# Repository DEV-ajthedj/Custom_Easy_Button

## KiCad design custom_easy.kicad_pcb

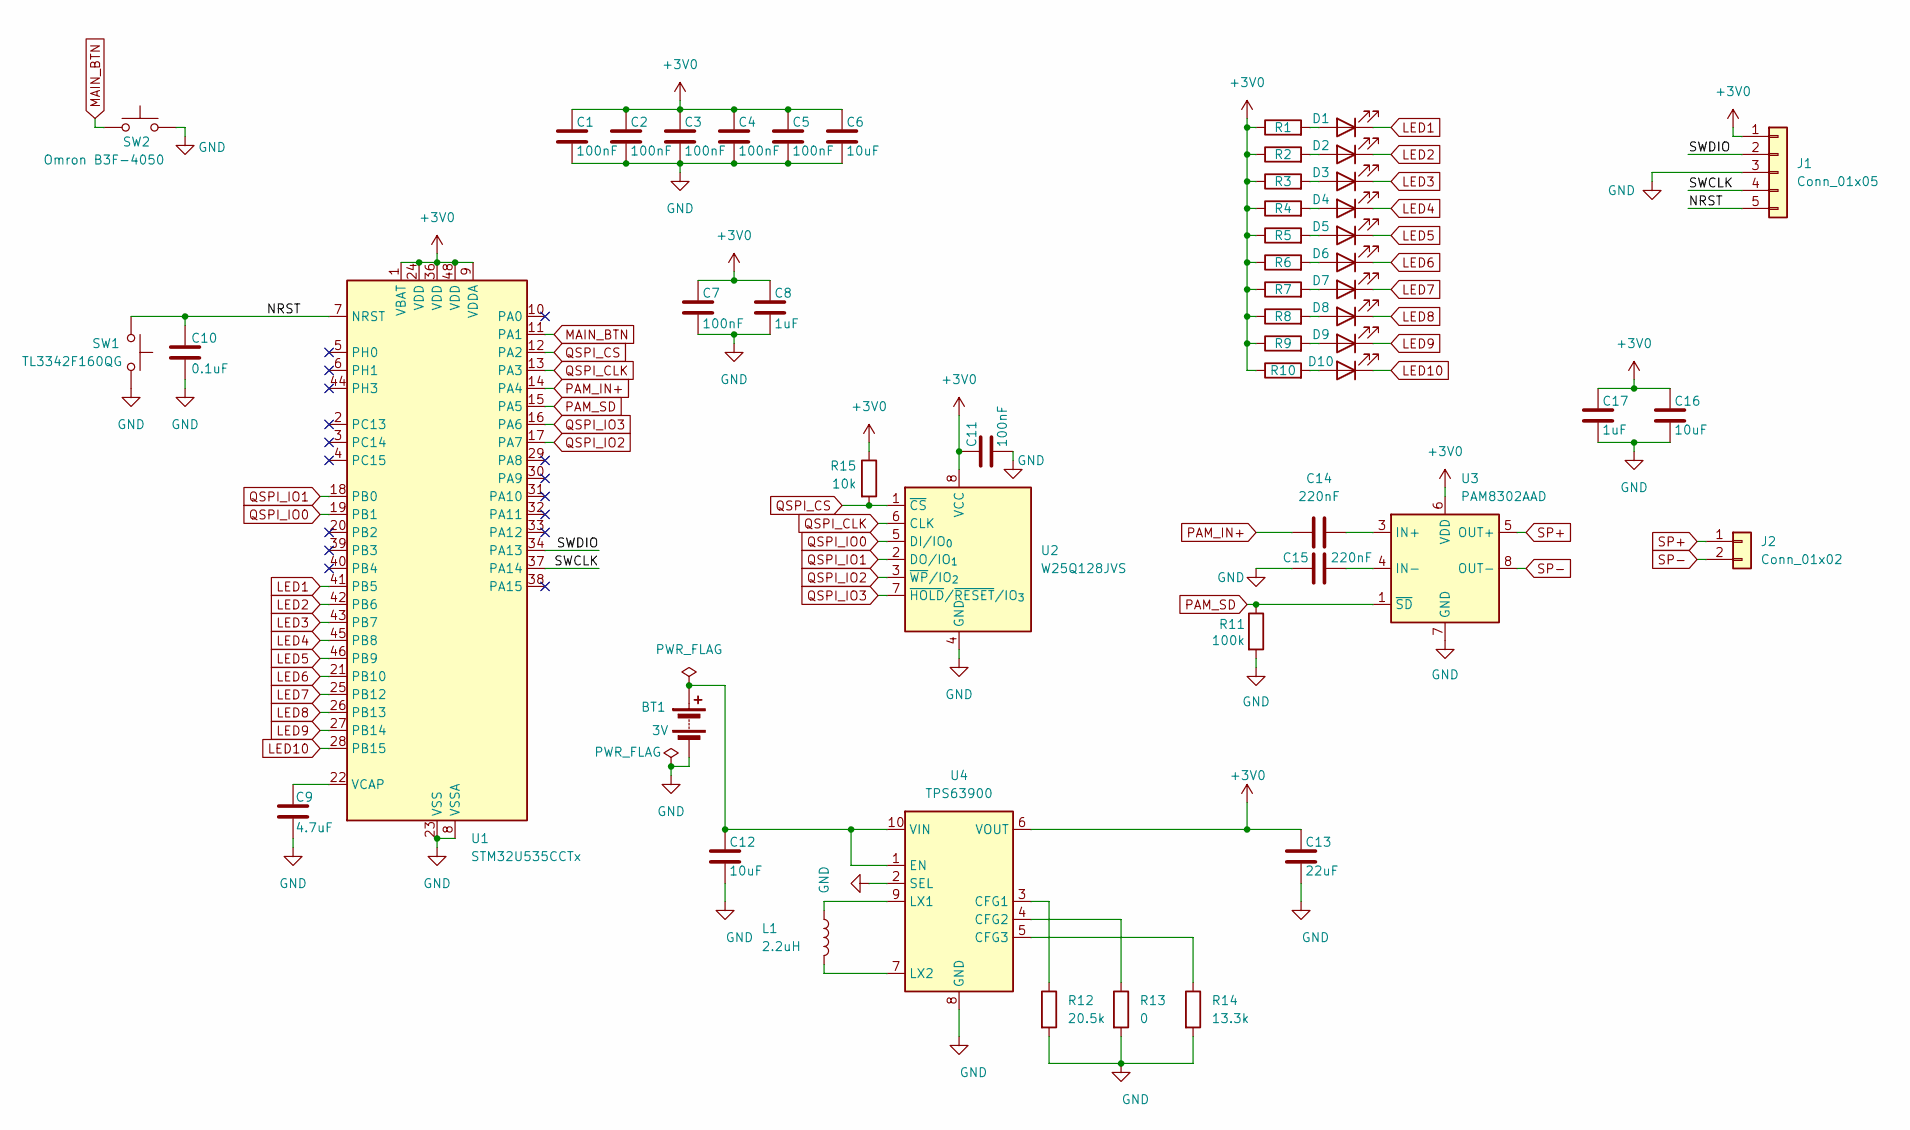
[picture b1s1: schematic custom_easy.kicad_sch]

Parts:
BT1: 3V; SolderWire-0.5sqmm_1x02_P4.6mm_D0.9mm_OD2.1mm
C1, C2, C3, C4, C5, C7, C11: 100nF; C_0603_1608Metric
C6, C16: 10uF; C_0805_2012Metric
C8, C17: 1uF; C_0603_1608Metric
C9: 4.7uF; C_0805_2012Metric
C10: 0.1uF; C_0603_1608Metric
C12: 10uF; C_0603_1608Metric; Voltage 10 V; MPN GRM188R61A106ME69D
C13: 22uF; C_0603_1608Metric; Voltage 6.3 V; MPN GRM187R60J226ME15D
C14, C15: 220nF; C_0603_1608Metric
D1, D2, D3, D4, D5, D6, D7, D8, D9, D10: APTD1608LSECK/J3-PF; LED_0603_1608Metric
J1: Conn_01x05; PinHeader_1x05_P2.54mm_Vertical
J2: Conn_01x02; SolderWire-0.5sqmm_1x02_P4.6mm_D0.9mm_OD2.1mm
L1: 2.2uH; L_Coilcraft_XxL4020; MPN XFL4020-222MEC
R1, R2, R3, R4, R5, R6, R7, R8, R9, R10: 620; R_0603_1608Metric
R11: 100k; R_0603_1608Metric
R12: 20.5k; R_0603_1608Metric; Tolerance 1%
R13: 0; R_0603_1608Metric
R14: 13.3k; R_0603_1608Metric; Tolerance 1%
R15: 10k; R_0603_1608Metric
SW1: TL3342F160QG; SW_SPST_TL3342
SW2: Omron B3F-4050; SW_SPST_Omron_B3F-40xx
U1: STM32U535CCTx; LQFP-48_7x7mm_P0.5mm
U2: W25Q128JVS; SOIC-8_5.3x5.3mm_P1.27mm
U3: PAM8302AAD; SOIC-8_3.9x4.9mm_P1.27mm
U4: TPS63900; WSON-10-1EP_2.5x2.5mm_P0.5mm_EP1.2x2mm_ThermalVias

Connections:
+3V0: C1.1, C2.1, C3.1, C4.1, C5.1, C6.1, C7.1, C8.1, C11.1, C13.1, C16.1, C17.1, J1.1, R1.1, R2.1, R3.1, R4.1, R5.1, R6.1, R7.1, R8.1, R9.1, R10.1, R15.1, U1.1 (VBAT), U1.9 (VDDA), U1.24 (VDD), U1.36 (VDD), U1.48 (VDD), U2.8 (VCC), U3.6 (VDD), U4.6 (VOUT)
/NRST: C10.1, J1.5, SW1.1, U1.7 (NRST)
/SWCLK: J1.4, U1.37 (PA14)
/SWDIO: J1.2, U1.34 (PA13)
GND: BT1.2 (-), C1.2, C2.2, C3.2, C4.2, C5.2, C6.2, C7.2, C8.2, C9.2, C10.2, C11.2, C12.2, C13.2, C15.1, C16.2, C17.2, J1.3, R11.2, R12.2, R13.2, R14.2, SW1.2, SW2.2, U1.8 (VSSA), U1.23 (VSS), U1.35 (VSS), U1.47 (VSS), U2.4 (GND), U3.7 (GND), U4.2 (SEL), U4.8 (GND), U4.11 (GND)
LED1: D1.1 (K), U1.41 (PB5)
LED2: D2.1 (K), U1.42 (PB6)
LED3: D3.1 (K), U1.43 (PB7)
LED4: D4.1 (K), U1.45 (PB8)
LED5: D5.1 (K), U1.46 (PB9)
LED6: D6.1 (K), U1.21 (PB10)
LED7: D7.1 (K), U1.25 (PB12)
LED8: D8.1 (K), U1.26 (PB13)
LED9: D9.1 (K), U1.27 (PB14)
LED10: D10.1 (K), U1.28 (PB15)
MAIN_BTN: SW2.1, U1.11 (PA1)
unnamed: BT1.1 (+), C12.1, U4.1 (EN), U4.10 (VIN)
unnamed: D1.2 (A), R1.2
unnamed: D2.2 (A), R2.2
unnamed: D3.2 (A), R3.2
unnamed: D4.2 (A), R4.2
unnamed: D5.2 (A), R5.2
unnamed: D6.2 (A), R6.2
unnamed: D7.2 (A), R7.2
unnamed: D8.2 (A), R8.2
unnamed: D9.2 (A), R9.2
unnamed: D10.2 (A), R10.2
unnamed: C9.1, U1.22 (VCAP)
unnamed: C14.2, U3.3 (IN+)
unnamed: C15.2, U3.4 (IN-)
unnamed: R12.1, U4.3 (CFG1)
unnamed: R13.1, U4.4 (CFG2)
unnamed: R14.1, U4.5 (CFG3)
unnamed: L1.1, U4.9 (LX1)
unnamed: L1.2, U4.7 (LX2)
PAM_IN+: C14.1, U1.14 (PA4)
PAM_SD: R11.1, U1.15 (PA5), U3.1 (~SD)
QSPI_CLK: U1.13 (PA3), U2.6 (CLK)
QSPI_CS: R15.2, U1.12 (PA2), U2.1 (~CS)
QSPI_IO0: U1.19 (PB1), U2.5 (DI/IO_{0})
QSPI_IO1: U1.18 (PB0), U2.2 (DO/IO_{1})
QSPI_IO2: U1.17 (PA7), U2.3 (~WP/IO_{2})
QSPI_IO3: U1.16 (PA6), U2.7 (~HOLD/~RESET/IO_{3})
SP+: J2.1, U3.5 (OUT+)
SP-: J2.2, U3.8 (OUT-)

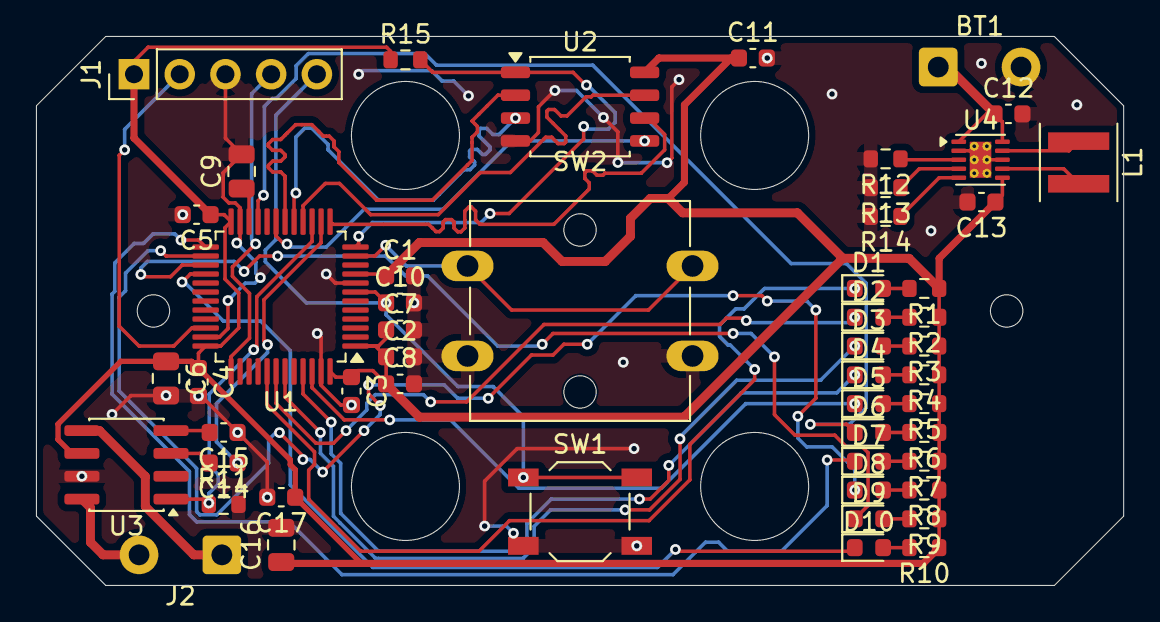
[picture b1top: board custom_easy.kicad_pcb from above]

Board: 2 copper layers, 60.4 x 30.5 mm, 52 parts (0 on the bottom side), 45 nets.
